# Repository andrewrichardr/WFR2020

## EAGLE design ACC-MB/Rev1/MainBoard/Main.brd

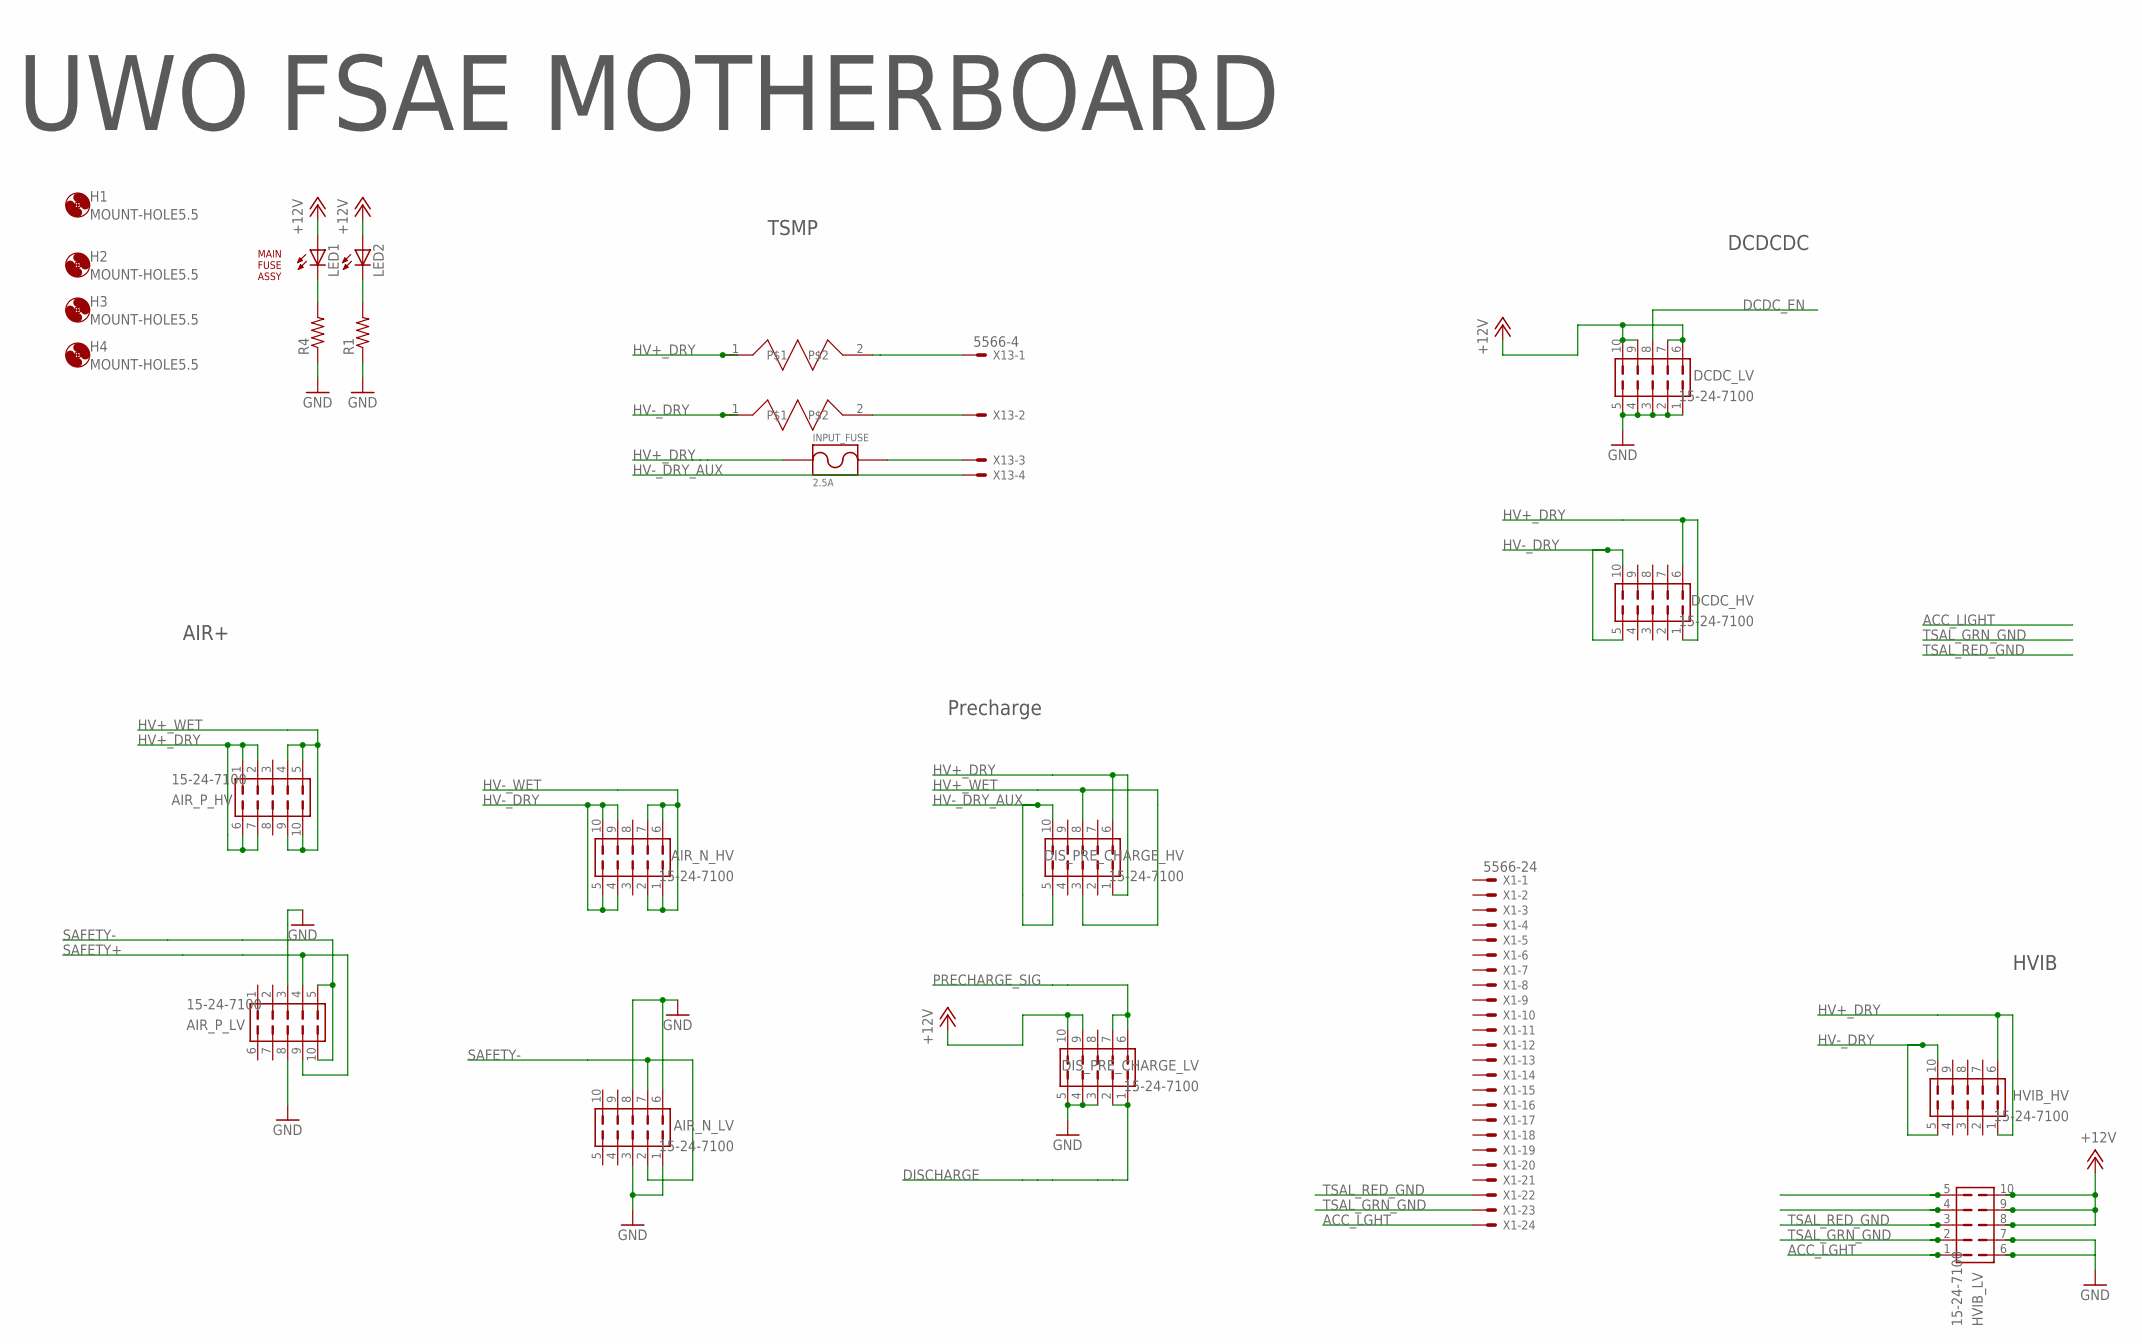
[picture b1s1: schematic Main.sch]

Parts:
AIR_N_HV: 15-24-7100; 5566-10-BMI
AIR_N_LV: 15-24-7100; 5566-10-BMI
AIR_P_HV: 15-24-7100; 5566-10-BMI
AIR_P_LV: 15-24-7100; 5566-10-BMI
DCDC_HV: 15-24-7100; 5566-10-BMI
DCDC_LV: 15-24-7100; 5566-10-BMI
DIS_PRE_CHARGE_HV: 15-24-7100; 5566-10-BMI
DIS_PRE_CHARGE_LV: 15-24-7100; 5566-10-BMI
H1, H2, H3, H4: MOUNT-HOLE5.5; 5,5
HVIB_HV: 15-24-7100; 5566-10-BMI
HVIB_LV: 15-24-7100; 5566-10-BMI
INPUT_FUSE: 2.5A; _CUSTOM_PARTS_LF_885
LED1, LED2: LED3MM
R1, R4: R-US_R0805; R0805
U$1: MAINFUSEASSY
U$3, U$4: TO247RESISTORHEATINK; _CUSTOM_TO-247-2V
X1: 5566-24
X13: 5566-4

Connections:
+12V: DCDC_LV.6, DCDC_LV.7, DCDC_LV.9, DCDC_LV.10, DIS_PRE_CHARGE_LV.9, DIS_PRE_CHARGE_LV.10, HVIB_LV.8, HVIB_LV.9, HVIB_LV.10, LED1.A, LED2.A
ACC_LGHT: HVIB_LV.1, X1.24
DCDC_EN: DCDC_LV.8
DISCHARGE: DIS_PRE_CHARGE_LV.1, DIS_PRE_CHARGE_LV.2
GND: AIR_N_LV.1, AIR_N_LV.3, AIR_N_LV.6, AIR_N_LV.8, AIR_P_LV.3, AIR_P_LV.8, DCDC_LV.1, DCDC_LV.2, DCDC_LV.3, DCDC_LV.4, DCDC_LV.5, DIS_PRE_CHARGE_LV.3, DIS_PRE_CHARGE_LV.4, DIS_PRE_CHARGE_LV.5, HVIB_LV.7, R1.1, R4.1
HV+_DRY: AIR_P_HV.1, AIR_P_HV.2, AIR_P_HV.6, AIR_P_HV.7, DCDC_HV.1, DCDC_HV.6, DIS_PRE_CHARGE_HV.1, DIS_PRE_CHARGE_HV.6, HVIB_HV.1, HVIB_HV.6, INPUT_FUSE.P$1, U$3.1
HV+_WET: AIR_P_HV.4, AIR_P_HV.5, AIR_P_HV.9, AIR_P_HV.10, DIS_PRE_CHARGE_HV.3, DIS_PRE_CHARGE_HV.8
HV-_DRY: AIR_N_HV.4, AIR_N_HV.5, AIR_N_HV.9, AIR_N_HV.10, DCDC_HV.5, DCDC_HV.10, HVIB_HV.5, HVIB_HV.10, U$4.1
HV-_DRY_AUX: DIS_PRE_CHARGE_HV.5, DIS_PRE_CHARGE_HV.10, X13.4
HV-_WET: AIR_N_HV.1, AIR_N_HV.2, AIR_N_HV.6, AIR_N_HV.7
unnamed: LED2.K (C), R1.2
unnamed: INPUT_FUSE.P$2, X13.3
unnamed: LED1.K (C), R4.2
unnamed: U$3.2, X13.1
unnamed: U$4.2, X13.2
PRECHARGE_SIG: DIS_PRE_CHARGE_LV.6, DIS_PRE_CHARGE_LV.7
SAFETY+: AIR_P_LV.4, AIR_P_LV.9
SAFETY-: AIR_N_LV.2, AIR_N_LV.7, AIR_P_LV.5, AIR_P_LV.10
TSAL_GRN_GND: HVIB_LV.2, X1.23
TSAL_RED_GND: HVIB_LV.3, X1.22

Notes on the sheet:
UWO FSAE MOTHERBOARD
DCDCDC
TSMP
AIR+
Precharge
HVIB

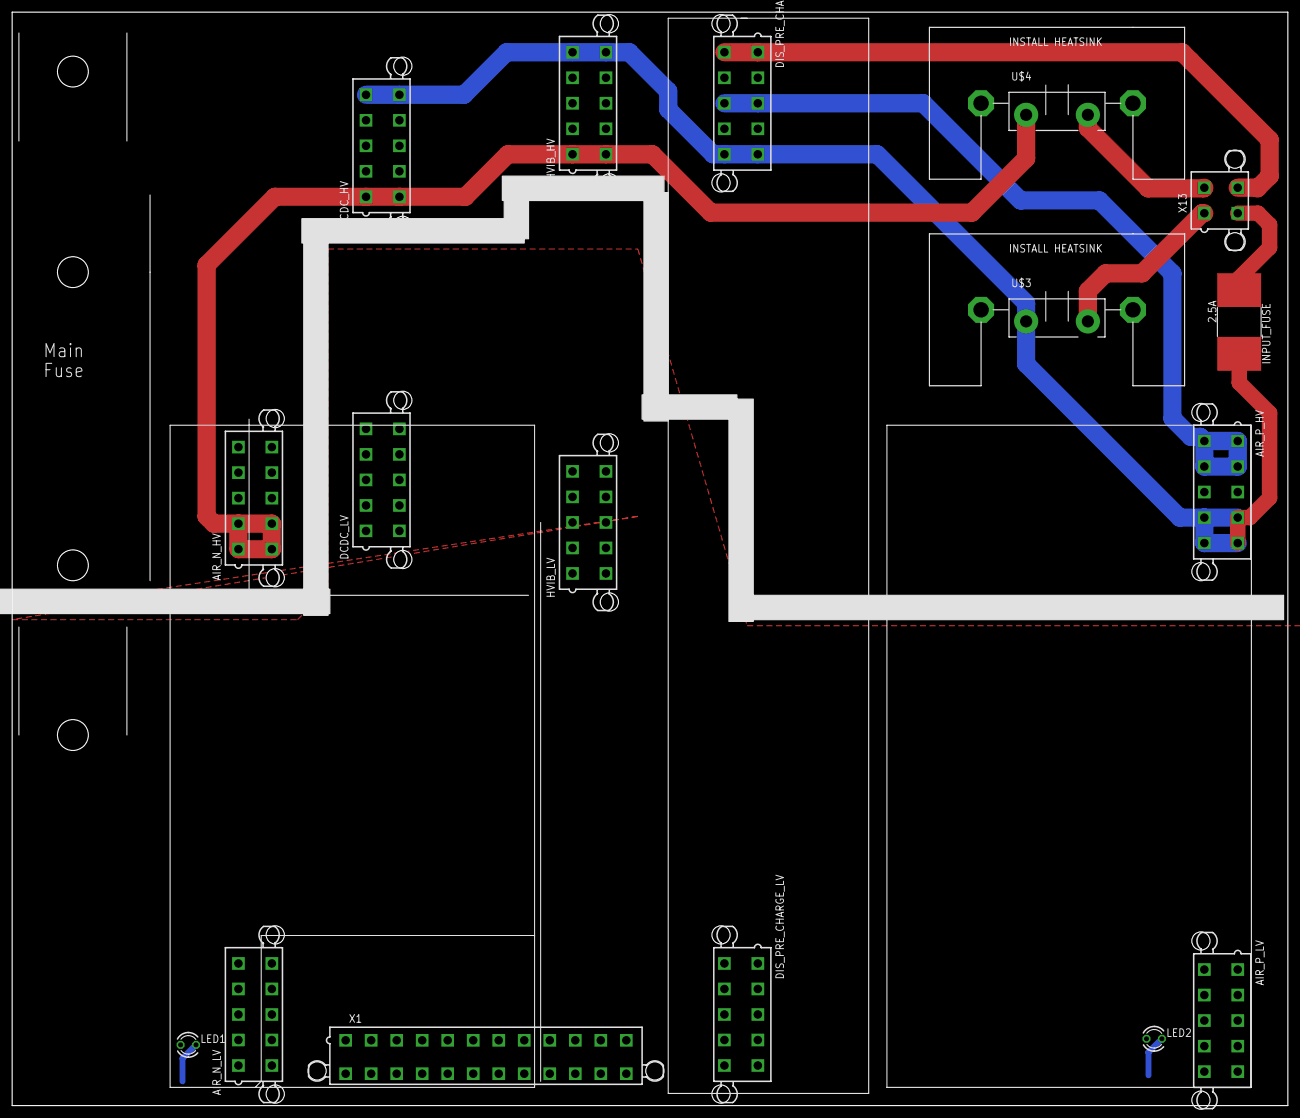
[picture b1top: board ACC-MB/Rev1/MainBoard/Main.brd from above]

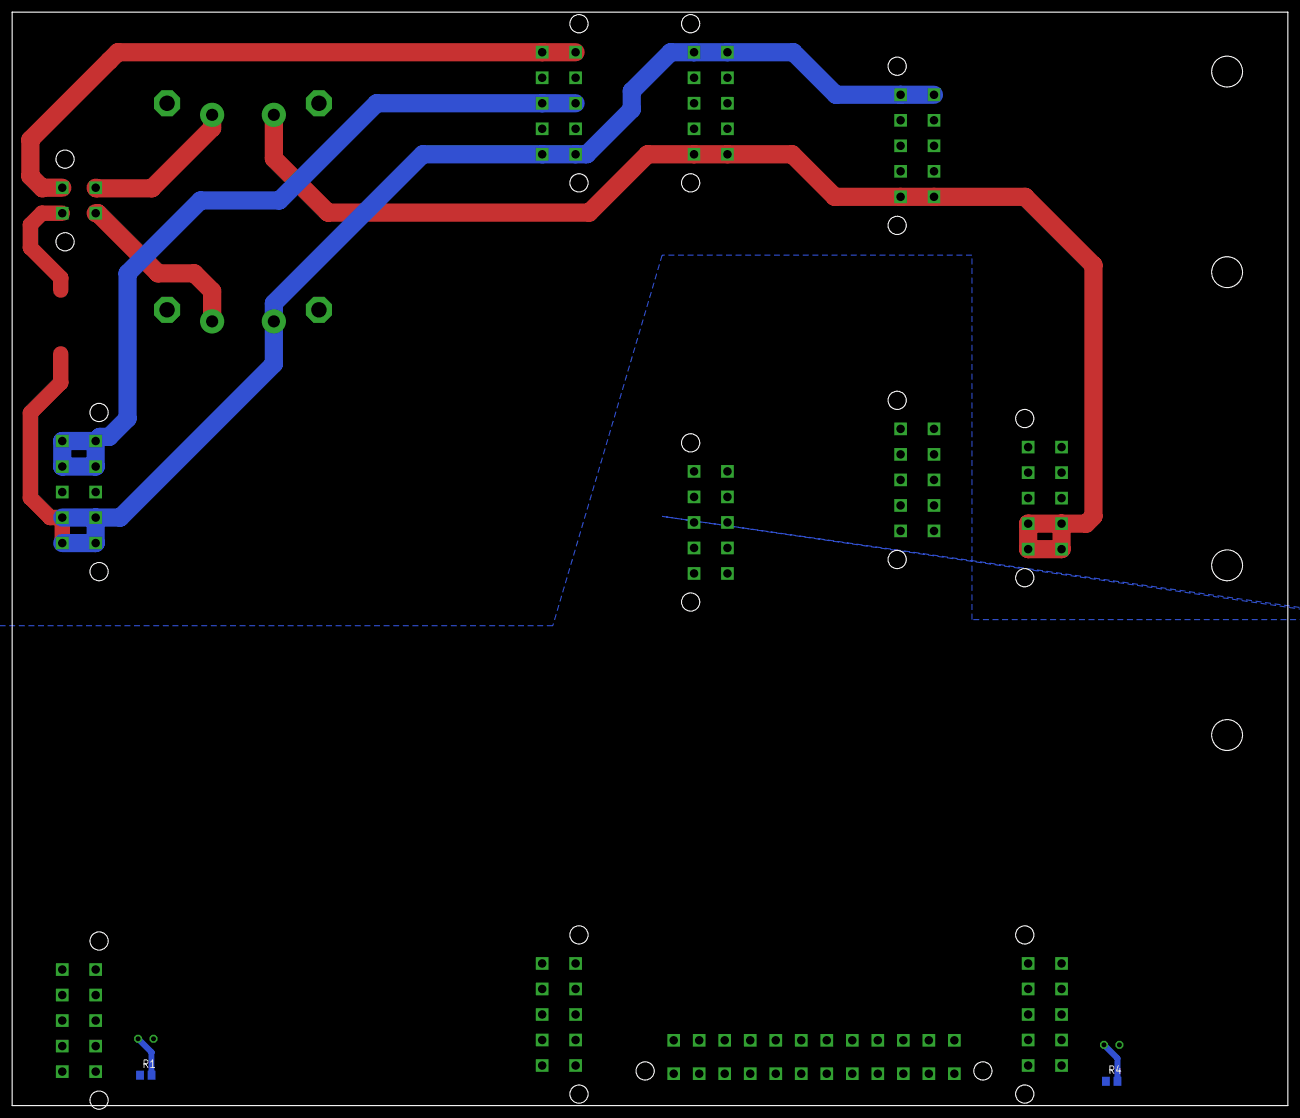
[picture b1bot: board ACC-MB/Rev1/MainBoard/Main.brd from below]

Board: 2 copper layers, 210.0 x 180.0 mm, 24 parts (2 on the bottom side), 19 nets.

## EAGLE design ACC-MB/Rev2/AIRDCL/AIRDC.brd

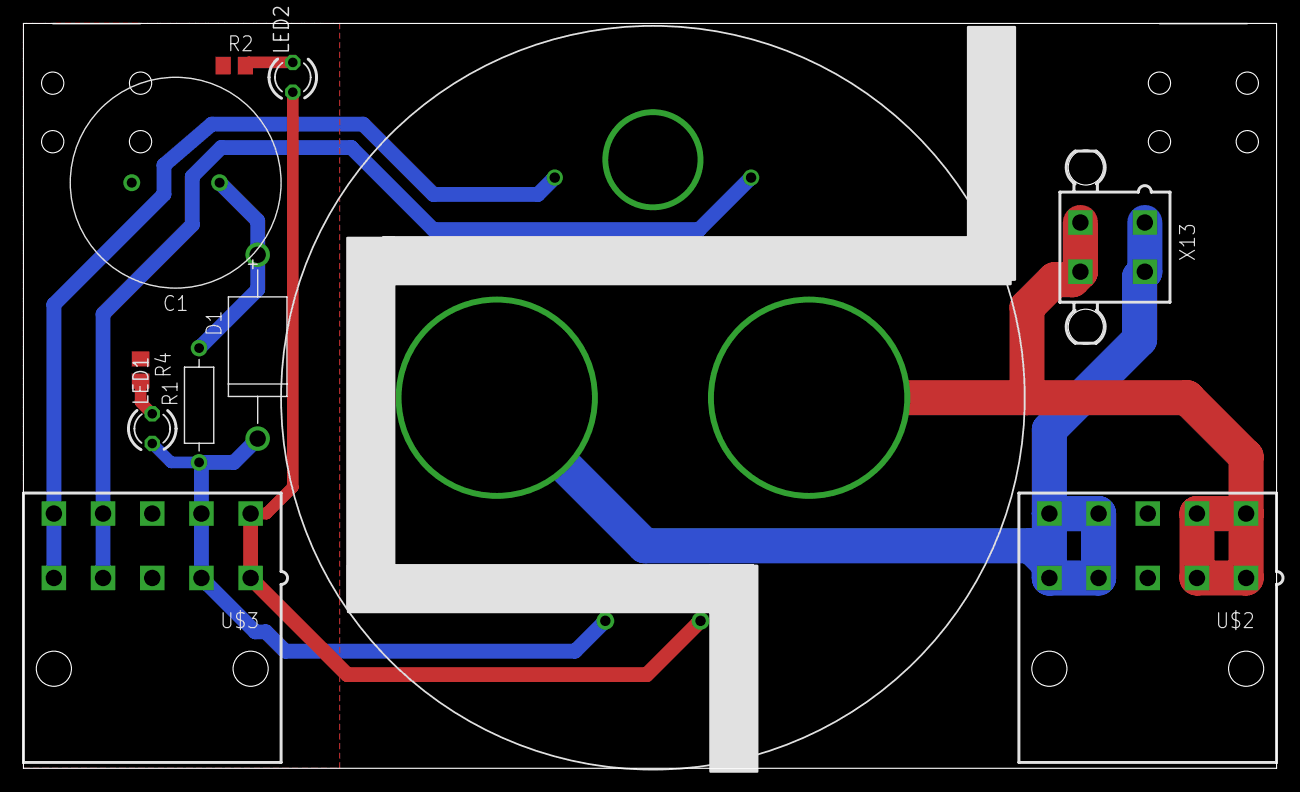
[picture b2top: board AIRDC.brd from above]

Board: 2 copper layers, 107.0 x 63.6 mm, 13 parts (0 on the bottom side), 10 nets.

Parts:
C1: 15000u; CAPPRD750W65D1800H3700B
D1: 10A; DIOAD1570W120L850D500B
LED1, LED2: LED3MM
R1: 100; RESAD976W63L650D250B
R2, R4: R0805
U$1: GV224
U$2, U$3: 15-24-6100
U$4, U$5: 7792
X13: 5566-4

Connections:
AUX_A1: U$1.A1, U$2.4, U$2.5, U$2.9, U$2.10, X13.1, X13.2
AUX_A2: U$1.A2, U$2.1, U$2.2, U$2.6, U$2.7, X13.3, X13.4
AUX_T1: U$1.T1, U$3.5, U$3.10
AUX_T2: U$1.T2, U$3.4, U$3.9
COIL_X1: D1.1, LED1.A, R1.1, U$1.X1, U$3.2, U$3.7
COIL_X2: LED2.A, U$1.X2, U$3.1, U$3.6
GND: C1.2, R2.1, R4.1, U$3.3, U$3.8
unnamed: LED2.K, R2.2
unnamed: C1.1, D1.2, R1.2
unnamed: LED1.K, R4.2

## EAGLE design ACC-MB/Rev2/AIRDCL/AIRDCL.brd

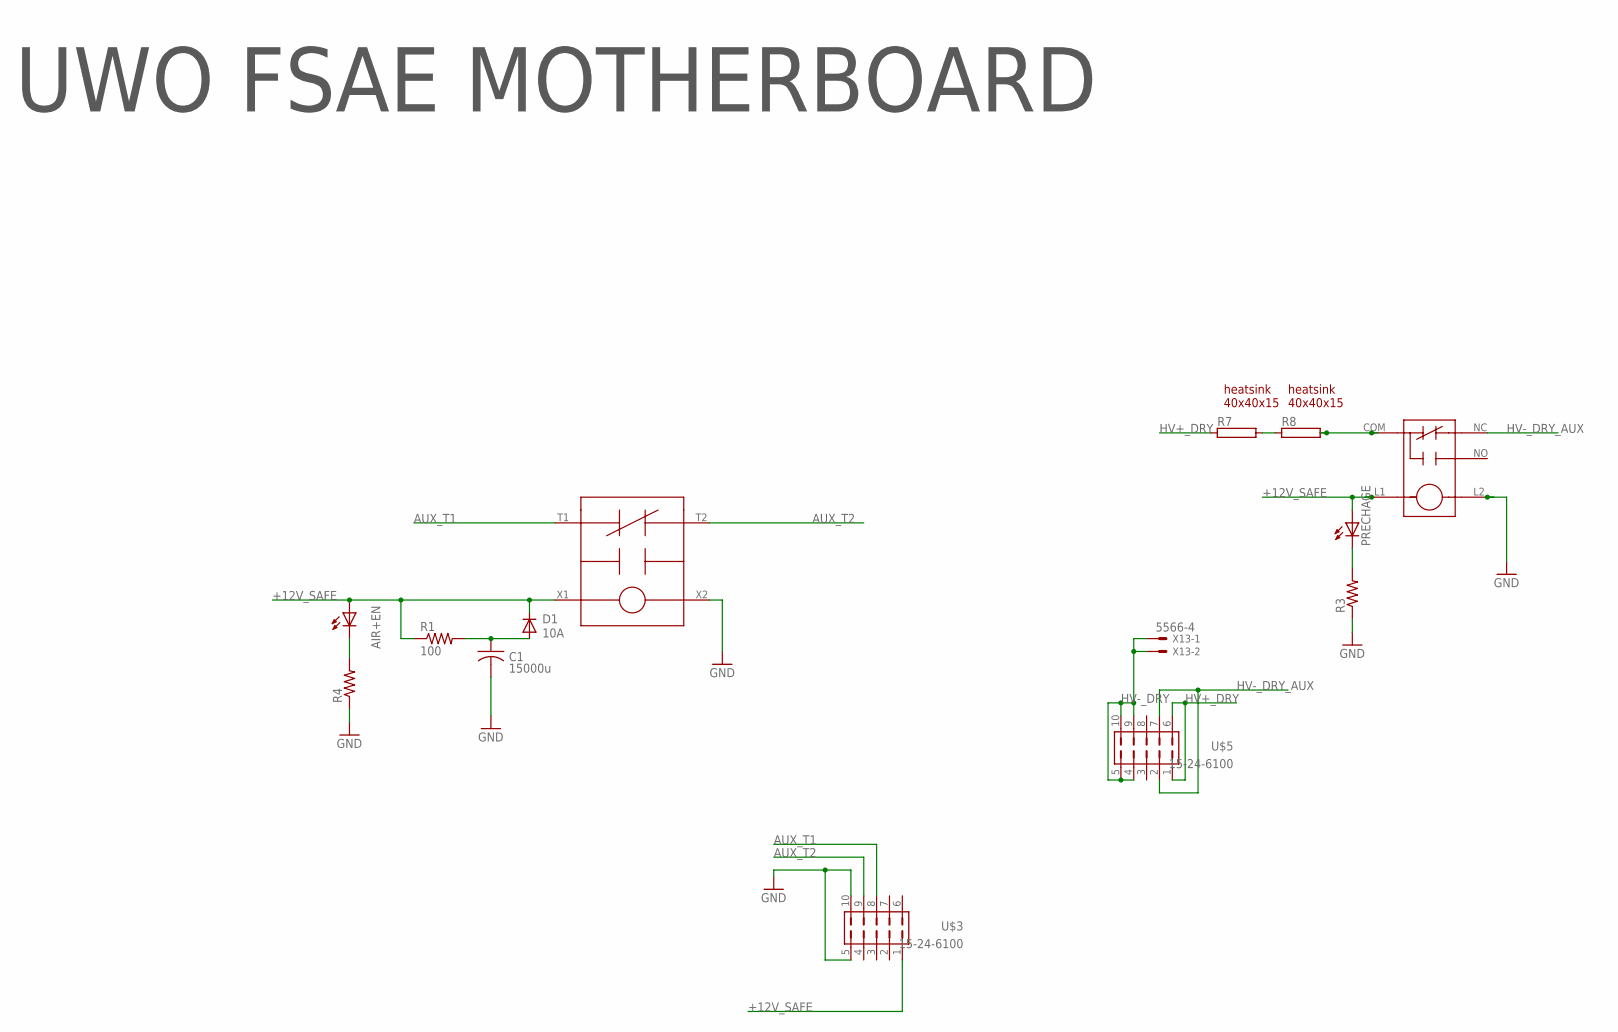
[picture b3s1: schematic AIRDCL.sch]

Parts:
AIR+EN: LED3MM
C1: 15000u; CAPPRD750W65D1800H3700B
D1: 10A; DIOAD1570W120L850D500B
PRECHAGE: LED3MM
R1: 100; RESAD976W63L650D250B
R3, R4: R-US_R0805; R0805
R7, R8: RMG100-H; TO-247-2H
U$1: GV224
U$2, U$8: HEATSINK40X40X15
U$3, U$5: 15-24-6100
U$4: G81C335
X13: 5566-4

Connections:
+12V_SAFE: AIR+EN.A, D1.1 (C), PRECHAGE.A, R1.1, U$1.X1, U$3.1, U$4.L1
AUX_T1: U$1.T1, U$3.8
AUX_T2: U$1.T2, U$3.9
GND: C1.2, R3.1, R4.1, U$1.X2, U$3.5, U$3.10, U$4.L2
HV+_DRY: R7.1, U$5.1, U$5.6
HV-_DRY: U$5.4, U$5.5, U$5.9, U$5.10, X13.1, X13.2
HV-_DRY_AUX: U$4.NC, U$5.2, U$5.7
unnamed: PRECHAGE.K (C), R3.2
unnamed: C1.1, D1.2 (A), R1.2
unnamed: AIR+EN.K (C), R4.2
unnamed: R7.2, R8.1
unnamed: R8.2, U$4.COM

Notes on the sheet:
UWO FSAE MOTHERBOARD

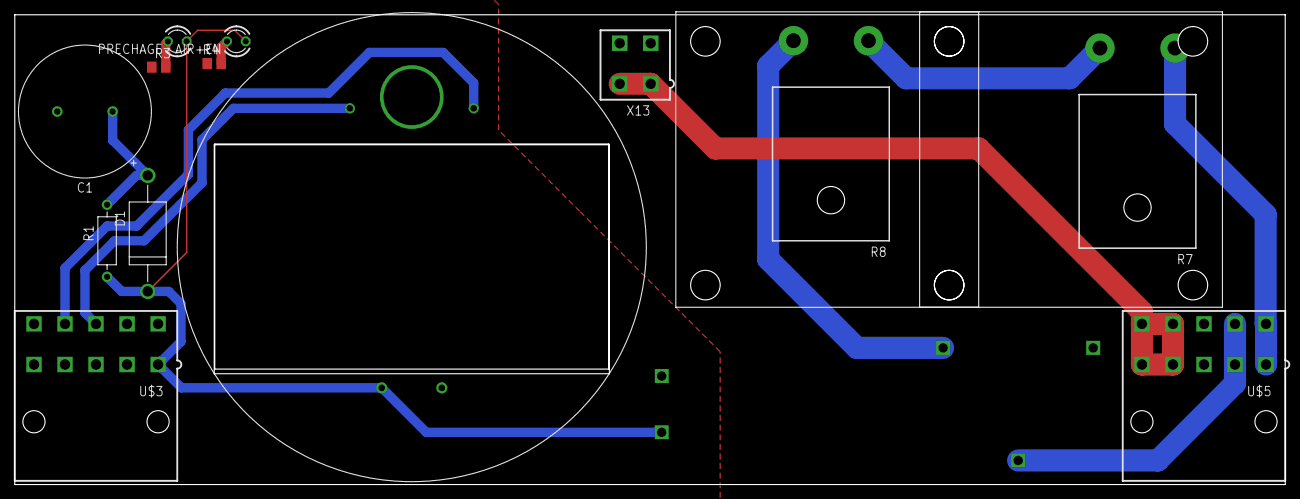
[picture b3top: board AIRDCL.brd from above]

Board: 2 copper layers, 172.0 x 63.6 mm, 16 parts (1 on the bottom side), 12 nets.

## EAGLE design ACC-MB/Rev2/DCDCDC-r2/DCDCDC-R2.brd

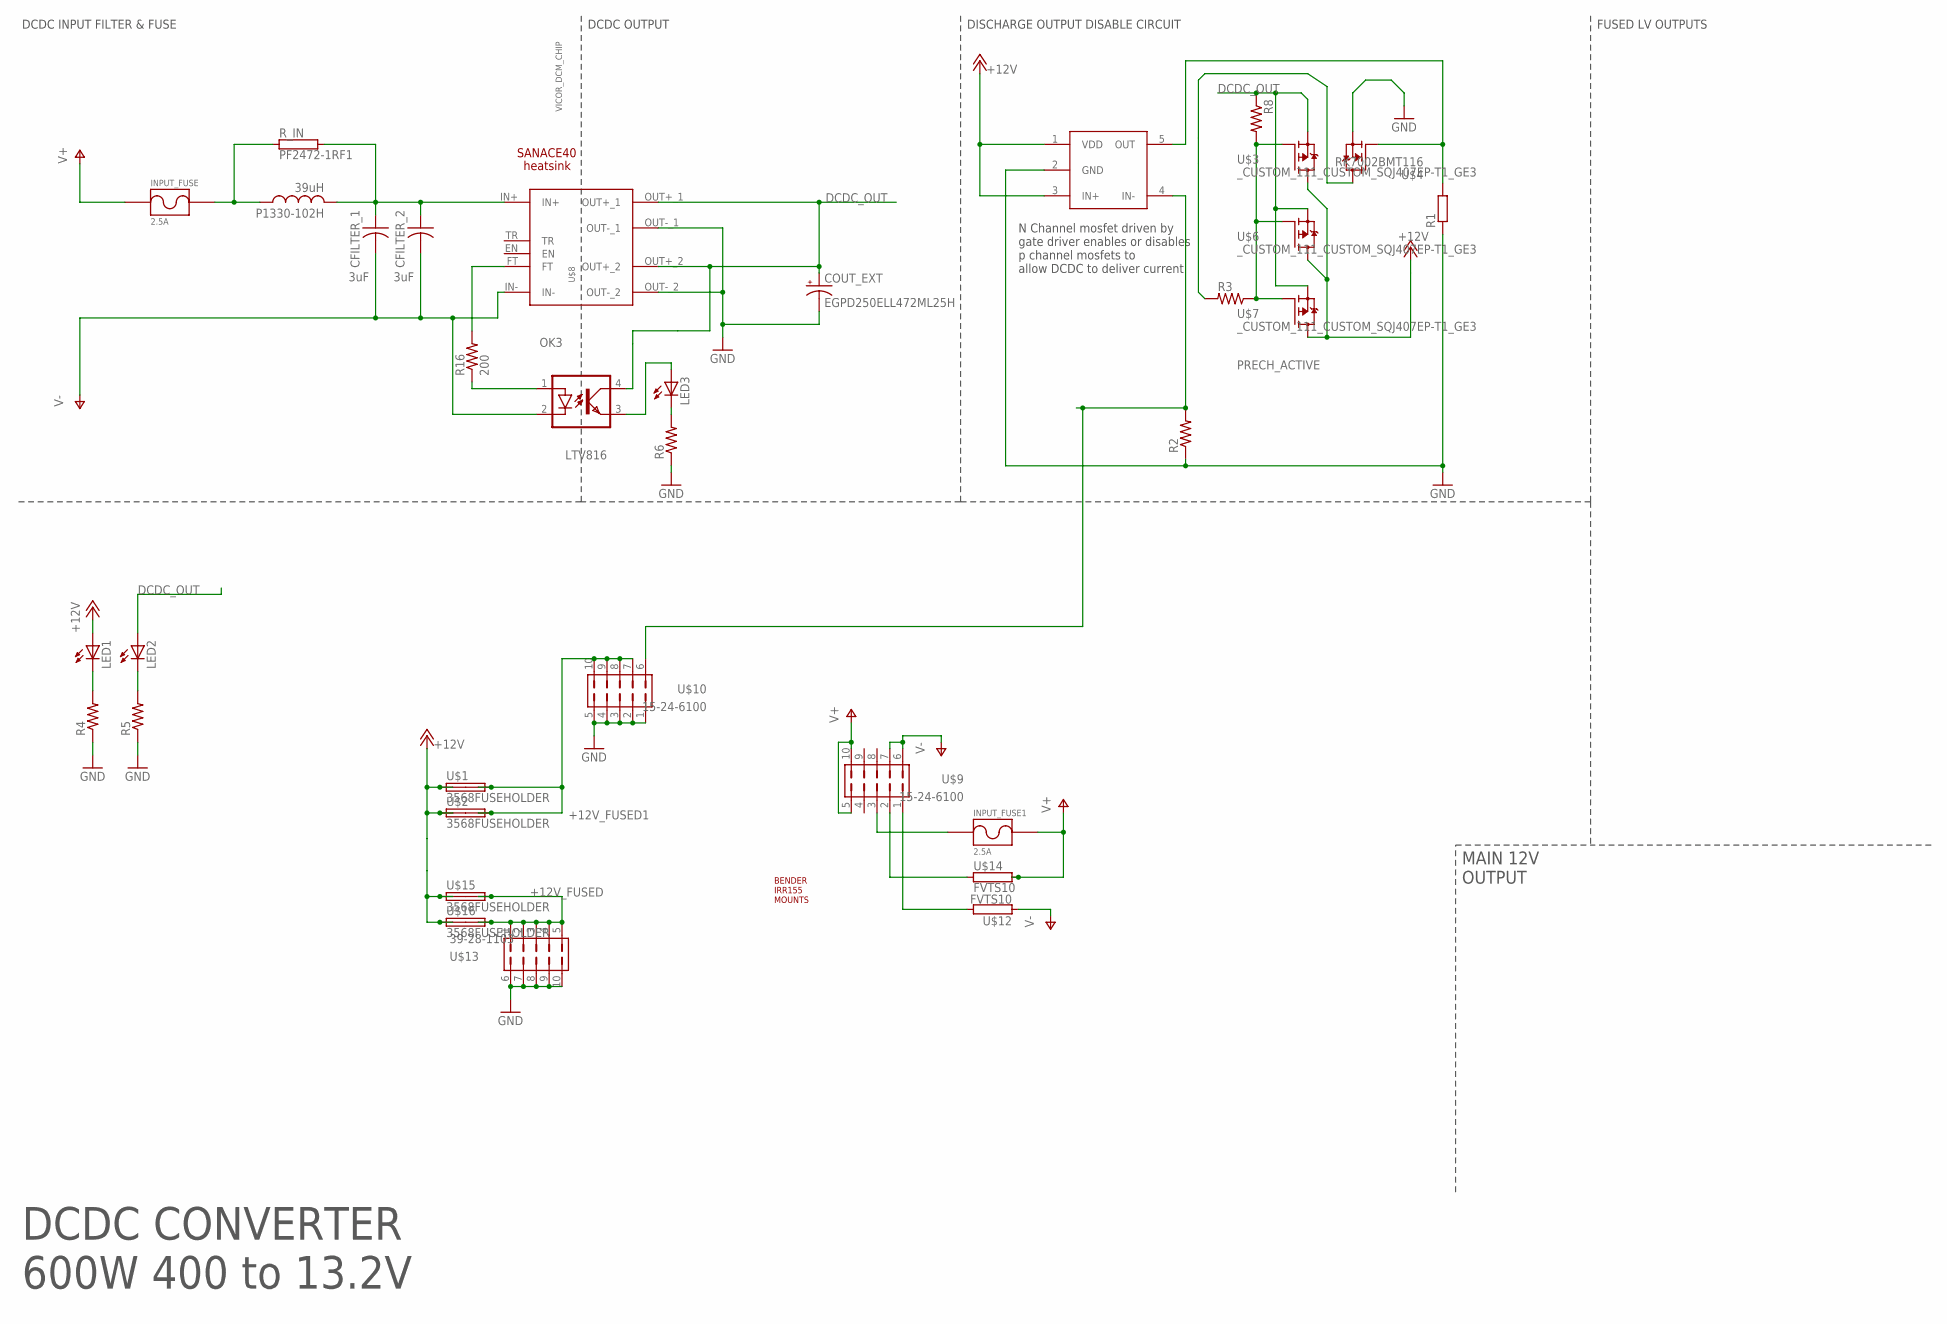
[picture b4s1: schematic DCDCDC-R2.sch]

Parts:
CFILTER_1, CFILTER_2: 3uF; CERALINK_FA3
COUT_EXT: EGPD250ELL472ML25H; E7,5-16
INPUT_FUSE, INPUT_FUSE1: 2.5A; _CUSTOM_PARTS_LF_885
LED1, LED2, LED3: LED3MM
OK3: LTV816; DIL04
P1330-102H: 39uH; L_1510_NONSTANDARD
R1: R-EU_R0805; R0805
R2, R3, R4, R5, R6, R8: R-US_R0805; R0805
R16: 200; R2010
R_IN: PF2472-1RF1; TO-247-2V
U$1, U$2, U$15, U$16: 3568FUSEHOLDER; 3568
U$3, U$6, U$7: _CUSTOM_111_CUSTOM_SQJ407EP-T1_GE3; _CUSTOM_111_CUSTOM_TRANS_SIRA90DP-T1-GE3
U$4: RK7002BMT116; SOT23
U$5: UCC27511AQDBVRQ1; SOT23-5L
U$8: VICOR_DCM_CHIP; VICOR_CHIP_HEATSINK
U$9, U$10: 15-24-6100
U$11: BENDER_IRR155
U$12, U$14: FVTS10
U$13: 39-28-1103
U$17: VICOR_HEATSINK_19MMLONG; VICOR_HEATSINK_19MM_LONG
U$18: SANACE40

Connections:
+12V: LED1.A, U$1.L1 (1A), U$1.L2 (1B), U$2.L1 (1A), U$2.L2 (1B), U$3.5 (D), U$5.1 (VDD), U$5.3 (IN+), U$6.5 (D), U$7.5 (D), U$15.L1 (1A), U$15.L2 (1B), U$16.L1 (1A), U$16.L2 (1B)
+12V_FUSED: U$13.1, U$13.2, U$13.3, U$13.4, U$13.5, U$15.R1 (2A), U$15.R2 (2B), U$16.R1 (2A), U$16.R2 (2B)
+12V_FUSED1: U$1.R1 (2A), U$1.R2 (2B), U$2.R1 (2A), U$2.R2 (2B), U$10.7, U$10.8, U$10.9, U$10.10
DCDC_OUT: COUT_EXT.+, LED2.A, OK3.4 (COL), R8.1, U$3.1 (S), U$3.2 (S), U$3.3 (S), U$6.1 (S), U$6.2 (S), U$6.3 (S), U$7.1 (S), U$7.2 (S), U$7.3 (S), U$8.OUT+_1, U$8.OUT+_2
GND: COUT_EXT.-, R1.1, R2.1, R4.1, R5.1, R6.1, U$4.2 (S), U$5.2 (GND), U$8.OUT-_1, U$8.OUT-_2, U$10.1, U$10.2, U$10.3, U$10.4, U$10.5, U$13.6, U$13.7, U$13.8, U$13.9, U$13.10
unnamed: R3.1, R8.2, U$3.4 (G), U$6.4 (G), U$7.4 (G)
unnamed: R1.2, U$4.1 (G), U$5.5 (OUT)
unnamed: CFILTER_1.P$1 (1), CFILTER_2.P$1 (1), P1330-102H.P$2 (2), R_IN.2, U$8.IN+
unnamed: R3.2, U$4.3 (D)
unnamed: LED1.K (C), R4.2
unnamed: LED2.K (C), R5.2
unnamed: R16.2, U$8.FT
unnamed: OK3.1 (A), R16.1
unnamed: LED3.K (C), R6.2
unnamed: LED3.A, OK3.3 (EMIT)
unnamed: INPUT_FUSE1.P$1, U$9.3
unnamed: U$9.2, U$14.P$1 (1)
unnamed: U$9.1, U$12.P$2 (2)
PRECH_ACTIVE: R2.2, U$5.4 (IN-), U$10.6
V+: INPUT_FUSE.P$1, INPUT_FUSE1.P$2, U$9.5, U$9.10, U$14.P$2 (2)
V+_FUSED: INPUT_FUSE.P$2, P1330-102H.P$1 (1), R_IN.1
V-: CFILTER_1.P$2 (2), CFILTER_2.P$2 (2), OK3.2 (C), U$8.IN-, U$9.6, U$9.7, U$12.P$1 (1)

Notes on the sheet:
DCDC CONVERTER 600W 400 to 13.2V
DISCHARGE OUTPUT DISABLE CIRCUIT
FUSED LV OUTPUTS
MAIN 12V OUTPUT
DCDC OUTPUT
DCDC INPUT FILTER & FUSE
N Channel mosfet driven by gate driver enables or disables p channel mosfets to allow DCDC to deliver current

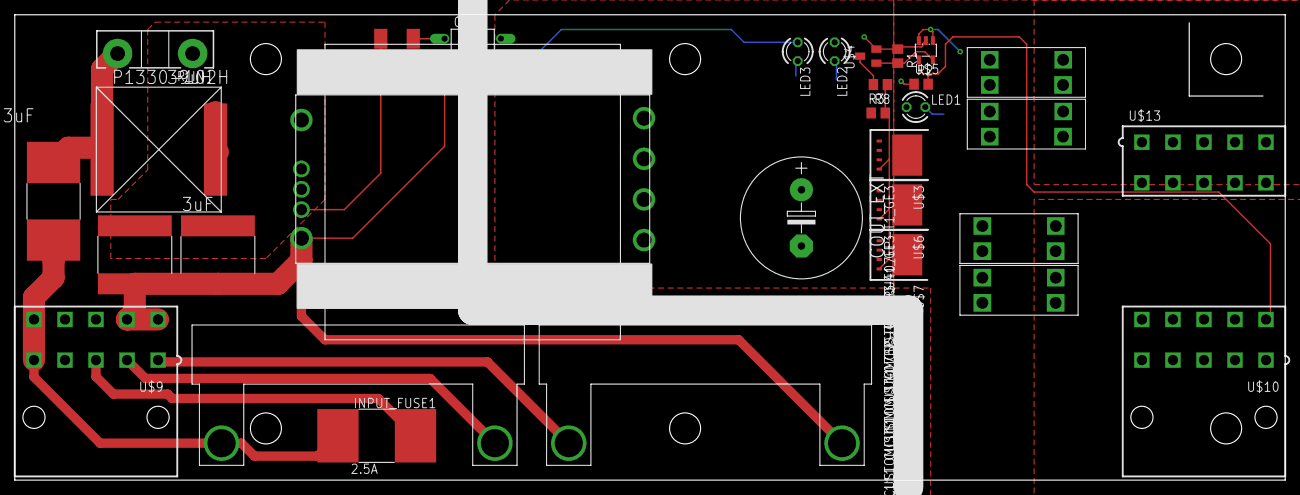
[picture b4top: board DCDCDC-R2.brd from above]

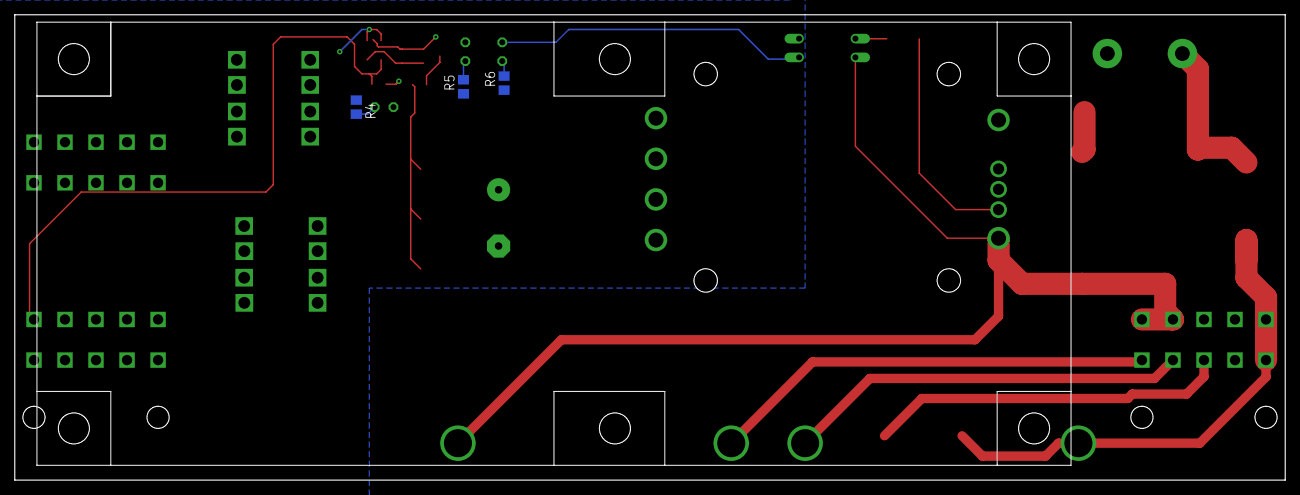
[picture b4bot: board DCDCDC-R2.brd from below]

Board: 2 copper layers, 172.0 x 63.0 mm, 37 parts (4 on the bottom side), 22 nets.

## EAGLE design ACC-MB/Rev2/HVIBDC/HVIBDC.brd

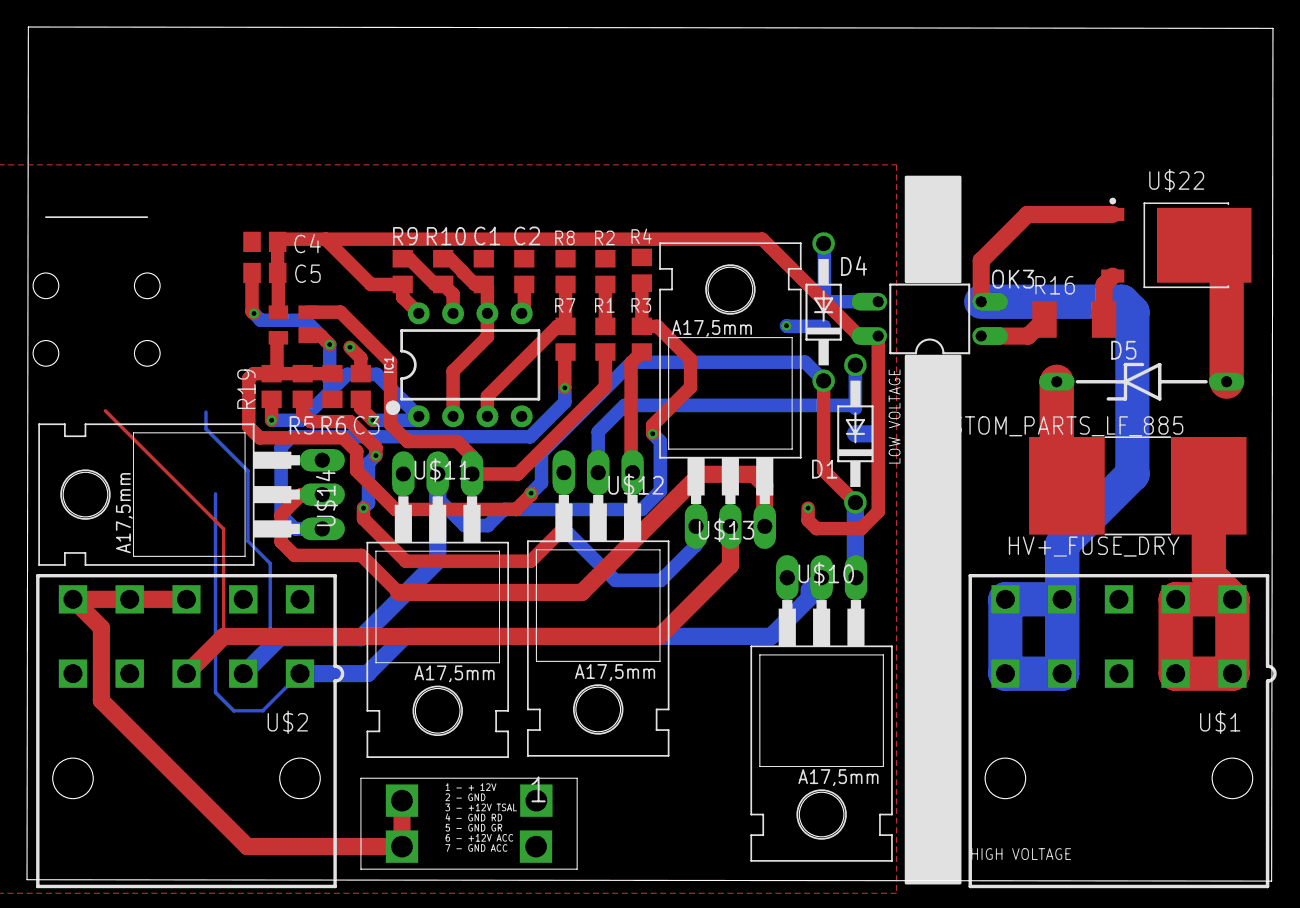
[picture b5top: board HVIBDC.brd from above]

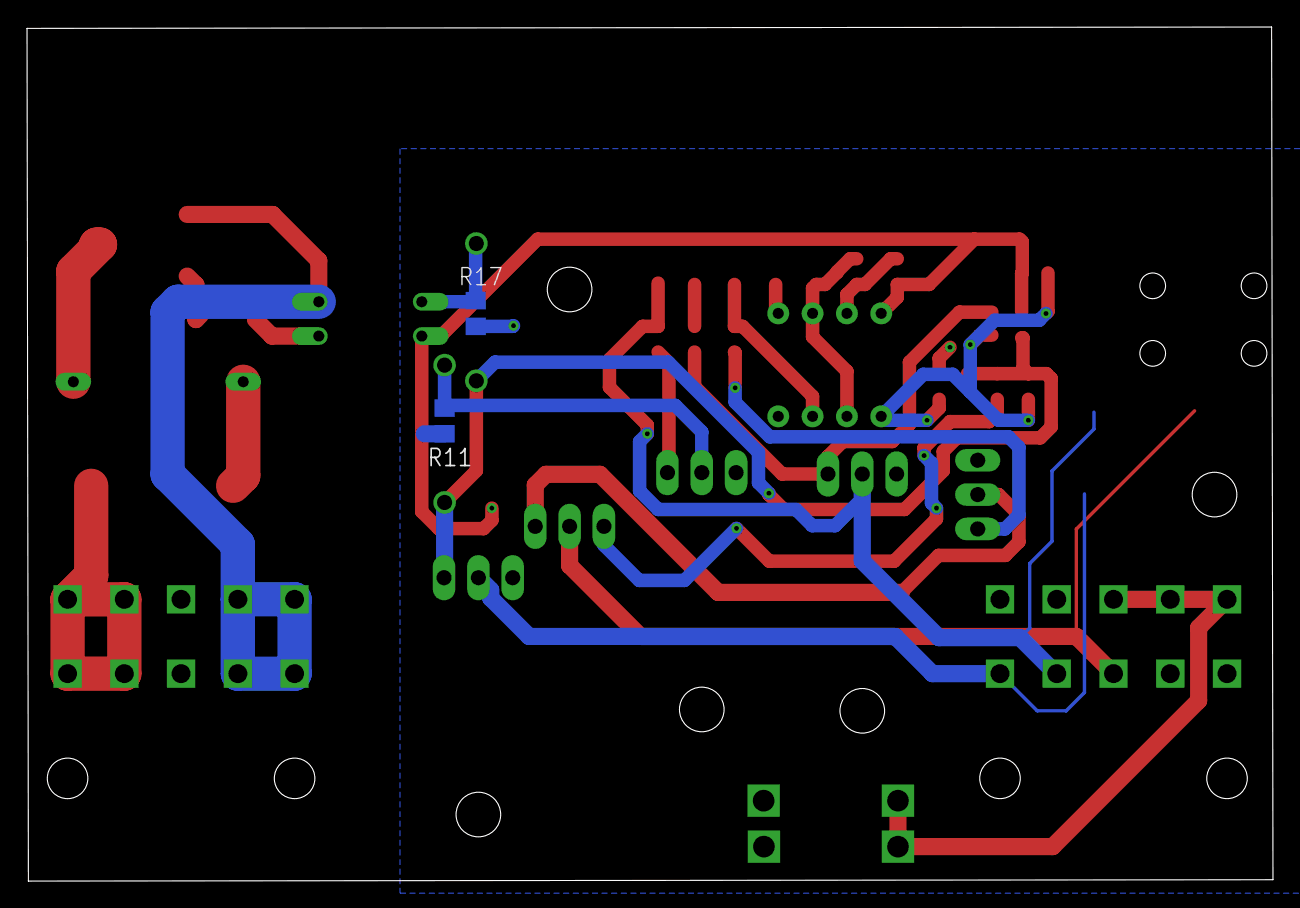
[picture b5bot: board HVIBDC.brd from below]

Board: 2 copper layers, 92.2 x 63.2 mm, 37 parts (2 on the bottom side), 25 nets.

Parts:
C1: 39n; C0805
C2: 10n; C0805
C3: 100n; C0805
C4: 4.7u; C0805
C5: 0.1u; C0805
D1, D4: 1N4004; DO41-10
D5: 1N4758A - 56Vz; ZDIO12.5
HV+_FUSE_DRY: _CUSTOM_PARTS_LF_885
IC1: 555; DIP08
OK3: LTV816; DIL04
R1, R3, R5, R7: 100; R0805
R2, R4, R6, R8, R11: 1M; R0805
R9: 2.2k; R0805
R10: 4.7M; R0805
R16: 200; R2010
R17, R19: 10k; R0805
U$1, U$2: 15-24-6100
U$3, U$4: 7792
U$5: 3568FUSEHOLDER; 3568
U$10, U$11, U$12, U$13, U$14: BUZ11; TO220
U$15: MIC4417; PDM_2019_REVB_MIC4416YM4-TR
U$22: _CUSTOM_IXCY10M90SD2PAK; TO228P991X238-3

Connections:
+12V: C3.1, C4.1, C5.1, IC1.4, IC1.8, OK3.4, R9.2, R11.2, U$5.R1, U$5.R2, U$15.VS
ACC_LGHT: U$2.1, U$10.2
AIR_ON: D1.C, D4.C, R5.1, R6.2, R19.2, U$10.1, U$15.CTL
GND: C1.2, C2.2, C3.2, C4.2, C5.2, IC1.1, R2.1, R4.1, R6.1, R8.1, R17.1, R19.1, U$2.4, U$2.5, U$2.6, U$2.7, U$10.3, U$11.3, U$12.3, U$14.3, U$15.GND
HV+_DRY_FUSED: D5.C, HV+_FUSE_DRY.P$1
unnamed: R1.1, R2.2
unnamed: R1.2, U$11.1, U$15.GATE
unnamed: R3.2, U$12.1
unnamed: C2.1, IC1.5
unnamed: IC1.7, R9.1, R10.2
unnamed: R5.2, U$13.1
unnamed: R7.2, U$14.1
unnamed: IC1.3, R7.1, R8.2
unnamed: C1.1, IC1.2, IC1.6, R10.1
unnamed: U$2.8, U$2.9, U$2.10, U$5.L1, U$5.L2
unnamed: U$13.3, U$14.2
unnamed: D4.A, OK3.3, R17.2
unnamed: D1.A, R11.1, U$12.2
unnamed: R16.2, U$22.2
unnamed: D5.A, U$22.3
unnamed: OK3.1, R16.1
TSAL_GRN_GND: R3.1, R4.2, U$2.2, U$11.2
TSAL_RED_GND: U$2.3, U$13.2
V+: HV+_FUSE_DRY.P$2, U$1.1, U$1.2, U$1.6, U$1.7
V-: OK3.2, U$1.4, U$1.5, U$1.9, U$1.10, U$22.1

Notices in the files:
parts and their libraries:
SparkFun-IC-Special-Function: Licensing: Creative Commons ShareAlike 4.0 International - https://creativecommons.org/licenses/by-sa/4.0
